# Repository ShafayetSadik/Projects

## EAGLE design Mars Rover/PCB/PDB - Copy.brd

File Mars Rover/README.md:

# Mars Rover

## Overview

Mars rover team designs, builds, and tests a semi-autonomous robotic system for simulated Mars exploration challenges. The rover must drive across rough terrain to GPS waypoints, operate without direct line of sight, manipulate real task panels with a robotic arm, collect and analyze soil or rock samples, deliver or retrieve objects, stream live video to a remote base station, and maintain a reliable wireless communication link for commands, sensor data, and control.

I was responsible for the electrical design and implementation, including PCB design and rover electrical integration. The PCB design files are attached in this repository. I also took part in developing the autonomous system with the software team.

## Autonomous Capability

The autonomy system is a ROS 2-based autonomous navigation stack for a Mars rover. It integrates GPS navigation, Pixhawk heading/GPS data, RealSense camera input, YOLO object detection, ArUco tag tracking, obstacle avoidance, and Arduino motor control into one modular rover system.

The stack is centered around the `local_planner`, which coordinates the rover mission flow. It follows GPS waypoints from the global planner, switches between autonomous and manual modes, starts search behaviors when needed, pauses/resumes perception nodes, and publishes velocity commands to `/cmd_vel`.

## Components Used

- ROS 2 autonomous navigation stack
- GPS waypoint navigation
- Pixhawk GPS, heading, and orientation data
- Arduino motor controller interface
- Intel RealSense camera
- YOLO object detection
- ArUco marker detection and tracking
- Depth-based obstacle avoidance
- Spiral search behavior
- Manual override through ROS 2 topics
- Gazebo and RViz simulation
- Custom ROS 2 messages and services
- Camera stream server
- Electrical design and PCB implementation
- Rover power and control PCB designs
- Robotic arm electrical design
- Wireless command, video, and sensor communication system

## Autonomous System Overview

### Main Features

- GPS waypoint navigation using mission targets from CSV
- Global and local planning for autonomous rover movement
- Pixhawk-based GPS and heading publishing
- Arduino serial interface for rover motor control
- RealSense camera support for depth sensing
- YOLO-based object detection for mission objects
- ArUco tag tracking and approach behavior
- Spiral search pattern for finding objects or tags near target locations
- Optional obstacle avoidance using depth data
- Manual override through ROS 2 topics
- Gazebo/RViz simulation support
- Custom ROS 2 messages and services for rover-specific data

### System Flow

1. Mission targets are loaded from `autonomous_nav/resource/targets.csv`.
2. `global_planner` publishes the target list as `/global_plan`.
3. `local_planner` follows each GPS waypoint using `/gps/fix` and heading data.
4. When a target is reached, the rover starts either object search or ArUco search.
5. `spiral_search` generates a GPS-based search pattern around the target area.
6. YOLO or ArUco tracking pauses the search when a target is detected and guides the rover toward it.
7. Movement commands are published to `/cmd_vel`.
8. `cmd_to_serial` sends rover velocity commands to the Arduino motor controller.

### Major Packages

- `autonomous_nav` - global planner, local planner, target handling, serial motor command bridge
- `pixhawk` - GPS, heading, and orientation publishing from Pixhawk
- `spiral_search` - GPS-based spiral search behavior
- `yolo_detection` - YOLO object detection with RealSense/USB camera input
- `aruco` - ArUco marker detection and approach control
- `obstacle_avoidance` - depth-image-based safe path and avoidance logic
- `custom_interfaces` - custom ROS 2 messages and services
- `cam_stream` - camera stream server
- `odometry` and `path_tracer` - rover path and odometry utilities
- `articubot_one` - Gazebo/RViz simulation package
- `realsense-ros` - Intel RealSense ROS 2 camera driver

## Preview

### Images

### PCB Designs

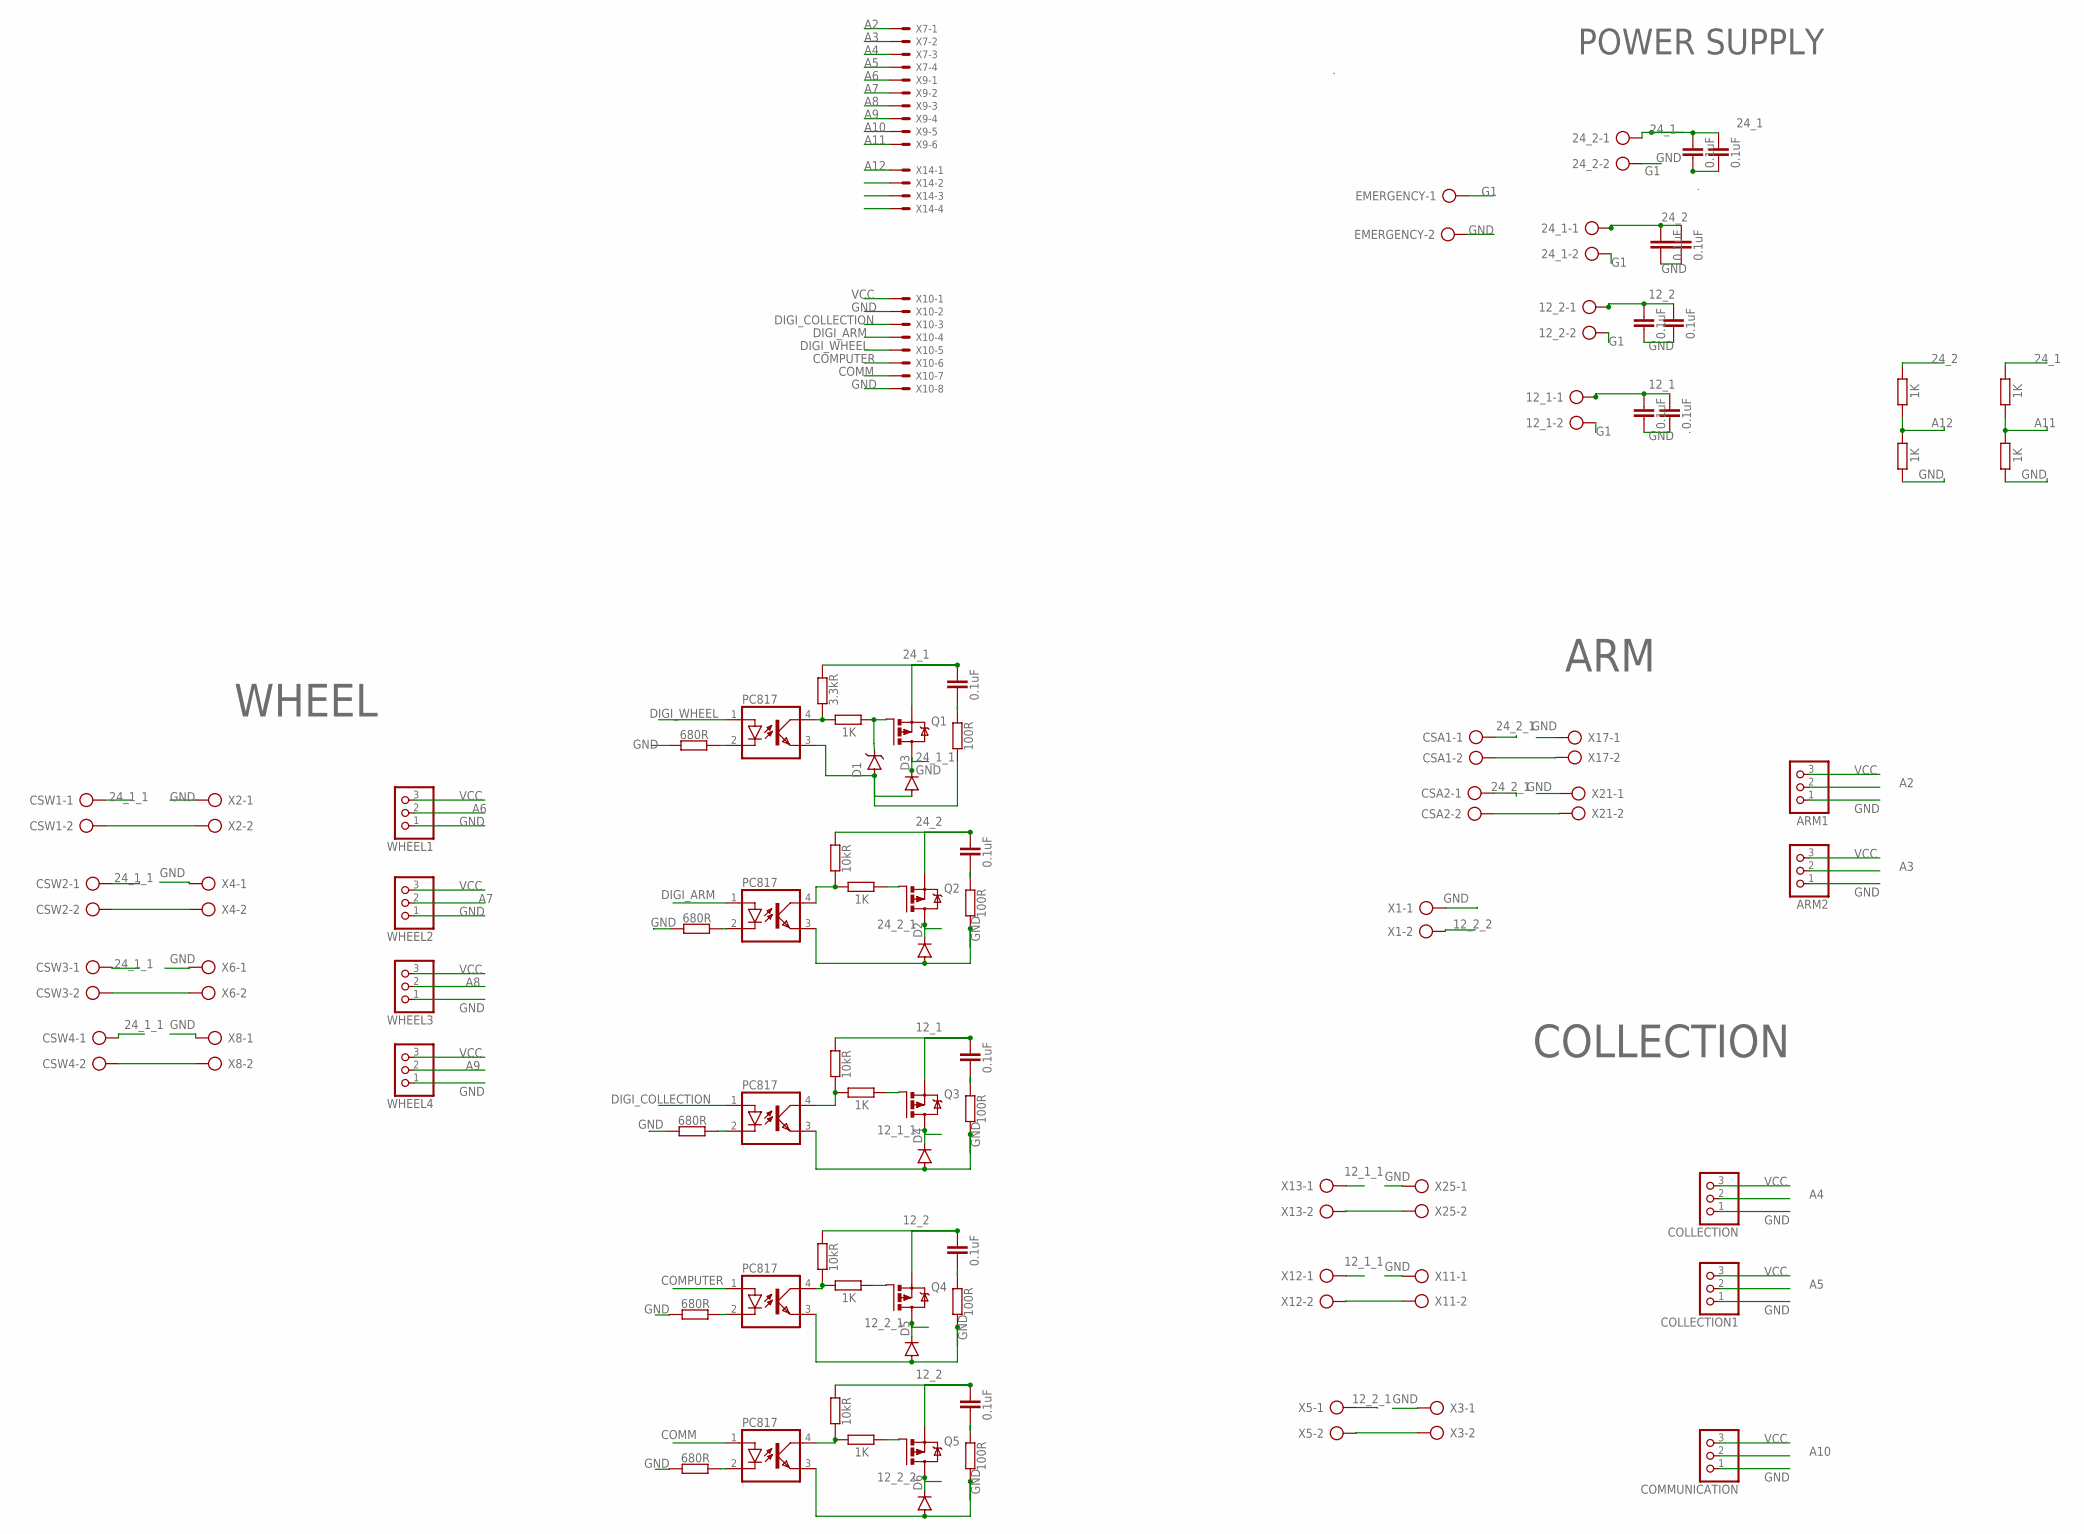
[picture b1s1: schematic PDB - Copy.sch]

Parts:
12_1, 12_2, 24_1, 24_2: AK300/2
ARM1, ARM2: PINHD-1X3; 1X03
C1, C2, C3, C4, C5, C6, C7, C8, C9, C10, C11, C18, C19: 0.1uF; C1206
COLLECTION, COLLECTION1: PINHD-1X3; 1X03
COMMUNICATION: PINHD-1X3; 1X03
CSA1, CSA2: AK300/2
CSW1, CSW2, CSW3, CSW4: AK300/2
D1: 1N4740A-TR; DO-41
D2, D3, D4, D5, D6: 1N4942; DO41-10
EMERGENCY: AK300/2
OK1, OK2, OK3, OK4, OK5: PC817; DIL04
Q1, Q2, Q3, Q4, Q5: PMOSFET-BACKUP_TO220; TO220BV
R1, R5, R9, R13, R24: 680R; R1206
R2, R7, R11, R15, R17, R18, R19, R20, R22: 1K; R1206
R3: 3.3kR; R1206
R4, R6, R10, R14, R21: 100R; R1206
R8, R12, R16, R23: 10kR; R1206
WHEEL1, WHEEL2, WHEEL3, WHEEL4: PINHD-1X3; 1X03
X1, X2, X3, X4, X5, X6, X8, X11, X12, X13, X17, X21, X25: AK300/2
X7, X14: JST-XH-04-PIN-LONG-PAD; JST-XH-04-PACKAGE-LONG-PAD
X9: JST-XH-06-PIN-LONG-PAD; JST-XH-06-PACKAGE-LONG-PAD
X10: JST-XH-08-PIN-LONG-PAD; JST-XH-08-PACKAGE-LONG-PAD

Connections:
12_1: 12_1.1, C3.2, C9.2, C10.2, Q3.S, R12.2
12_1_1: D4.C, Q3.D, X12.1, X13.1
12_2: 12_2.1, C4.2, C5.2, C6.2, C11.2, Q4.S, Q5.S, R16.2, R23.2
12_2_1: D5.C, Q4.D, X5.1
12_2_2: D6.C, Q5.D, X1.2
24_1: 24_2.1, C1.2, C7.2, C8.2, Q1.S, R3.2, R19.2
24_1_1: CSW1.1, CSW2.1, CSW3.1, CSW4.1, D3.C, Q1.D
24_2: 24_1.1, C2.2, C18.2, C19.2, Q2.S, R8.2, R17.2
24_2_1: CSA1.1, CSA2.1, D2.C, Q2.D
A2: ARM1.2, X7.1
A3: ARM2.2, X7.2
A4: COLLECTION.2, X7.3
A5: COLLECTION1.2, X7.4
A6: WHEEL1.2, X9.1
A7: WHEEL2.2, X9.2
A8: WHEEL3.2, X9.3
A9: WHEEL4.2, X9.4
A10: COMMUNICATION.2, X9.5
A11: R19.1, R20.2, X9.6
A12: R17.1, R18.2, X14.1
COMM: OK5.1 (A), X10.7
COMPUTER: OK4.1 (A), X10.6
DIGI_ARM: OK2.1 (A), X10.4
DIGI_COLLECTION: OK3.1 (A), X10.3
DIGI_WHEEL: OK1.1 (A), X10.5
G1: 12_1.2, 12_2.2, 24_1.2, 24_2.2, EMERGENCY.1
GND: ARM1.1, ARM2.1, C5.1, C6.1, C7.1, C8.1, C9.1, C10.1, C18.1, C19.1, COLLECTION.1, COLLECTION1.1, COMMUNICATION.1, D1.A, D2.A, D3.A, D4.A, D5.A, D6.A, EMERGENCY.2, OK1.3 (EMIT), OK2.3 (EMIT), OK3.3 (EMIT), OK4.3 (EMIT), OK5.3 (EMIT), R1.2, R4.1, R5.2, R6.1, R9.2, R10.1, R13.2, R14.1, R18.1, R20.1, R21.1, R24.2, WHEEL1.1, WHEEL2.1, WHEEL3.1, WHEEL4.1, X1.1, X2.1, X3.1, X4.1, X6.1, X8.1, X10.2, X10.8, X11.1, X17.1, X21.1, X25.1
unnamed: OK1.4 (COL), R2.1, R3.1
unnamed: OK4.2 (C), R13.1
unnamed: OK3.2 (C), R9.1
unnamed: OK2.4 (COL), R7.1, R8.1
unnamed: C2.1, R6.2
unnamed: OK3.4 (COL), R11.1, R12.1
unnamed: C4.1, R14.2
unnamed: C3.1, R10.2
unnamed: Q4.G, R15.2
unnamed: OK4.4 (COL), R15.1, R16.1
unnamed: C11.1, R21.2
unnamed: OK5.4 (COL), R22.1, R23.1
unnamed: Q5.G, R22.2
unnamed: OK2.2 (C), R5.1
unnamed: OK1.2 (C), R1.1
unnamed: X11.2, X12.2
unnamed: Q2.G, R7.2
unnamed: OK5.2 (C), R24.1
unnamed: Q3.G, R11.2
unnamed: CSW1.2, X2.2
unnamed: CSW2.2, X4.2
unnamed: C1.1, R4.2
unnamed: D1.C, Q1.G, R2.2
unnamed: CSW3.2, X6.2
unnamed: CSW4.2, X8.2
unnamed: CSA1.2, X17.2
unnamed: CSA2.2, X21.2
unnamed: X13.2, X25.2
unnamed: X3.2, X5.2
VCC: ARM1.3, ARM2.3, COLLECTION.3, COLLECTION1.3, COMMUNICATION.3, WHEEL1.3, WHEEL2.3, WHEEL3.3, WHEEL4.3, X10.1

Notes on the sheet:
WHEEL
ARM
COLLECTION
POWER SUPPLY

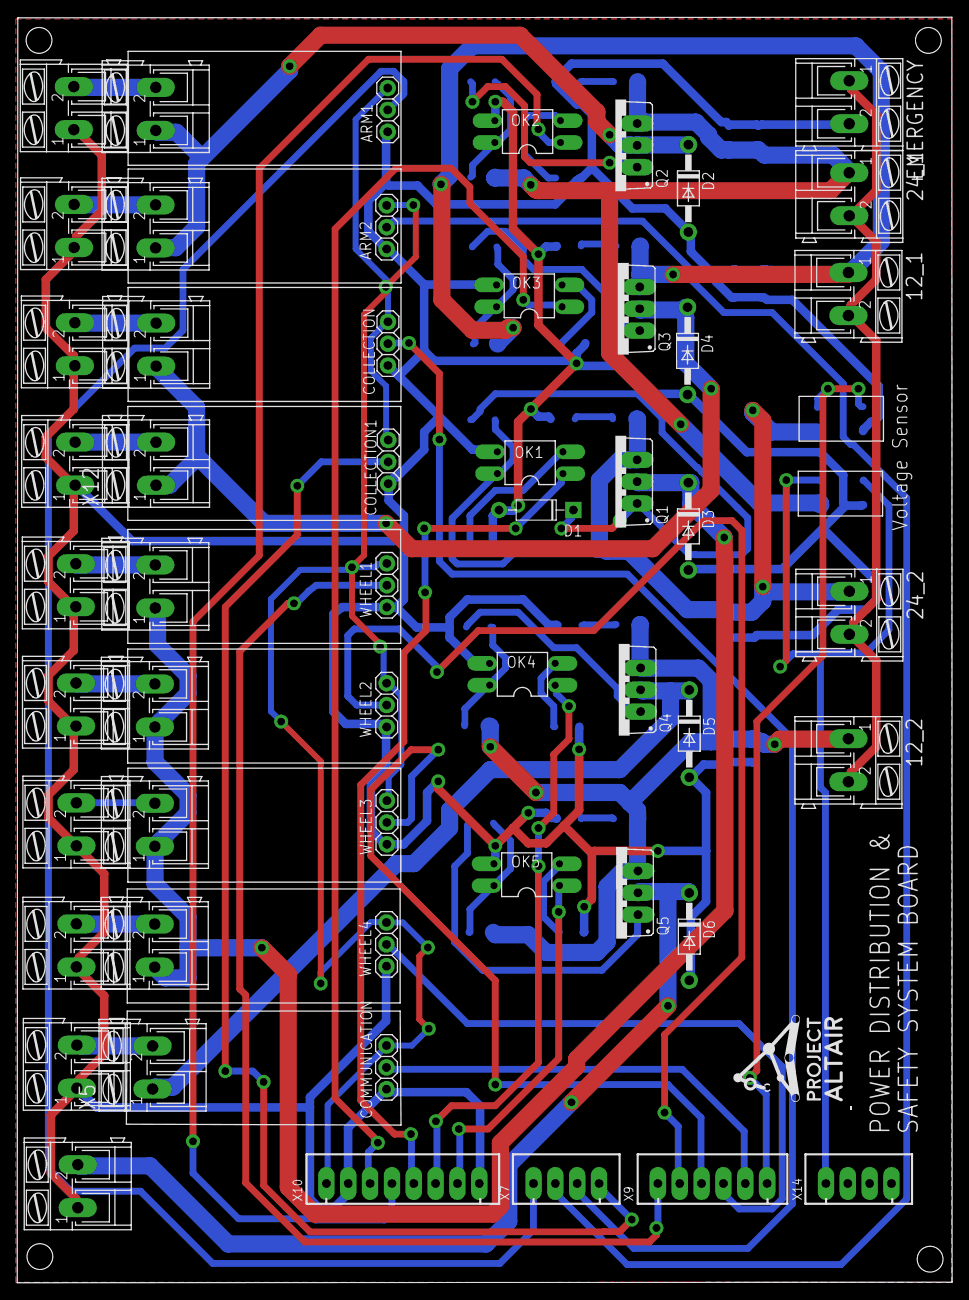
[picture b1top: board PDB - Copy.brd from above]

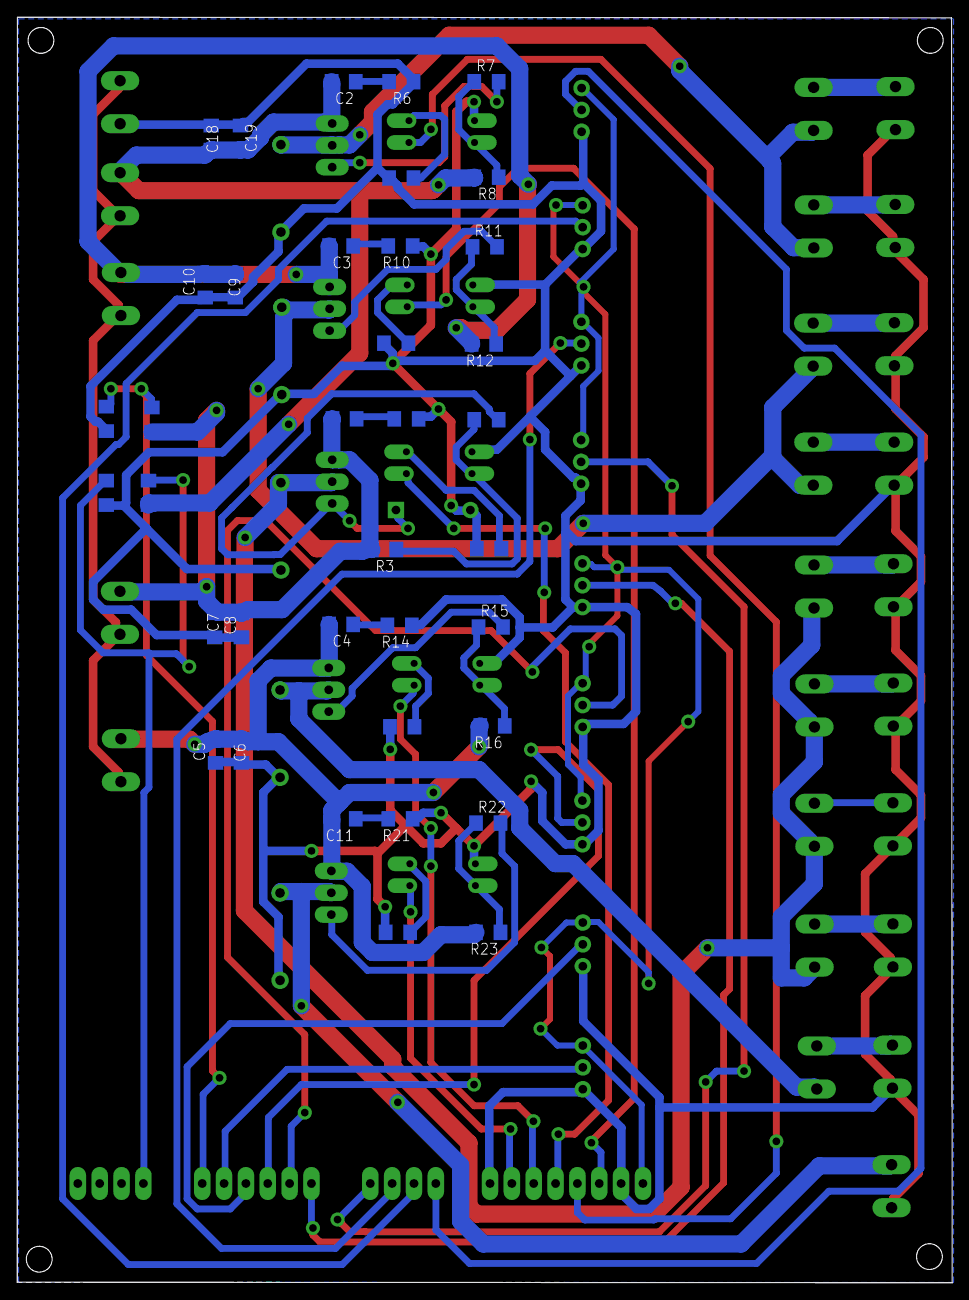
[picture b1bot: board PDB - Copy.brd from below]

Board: 2 copper layers, 108.7 x 147.1 mm, 91 parts (37 on the bottom side), 57 nets.

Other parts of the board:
U$2: ALTAIR

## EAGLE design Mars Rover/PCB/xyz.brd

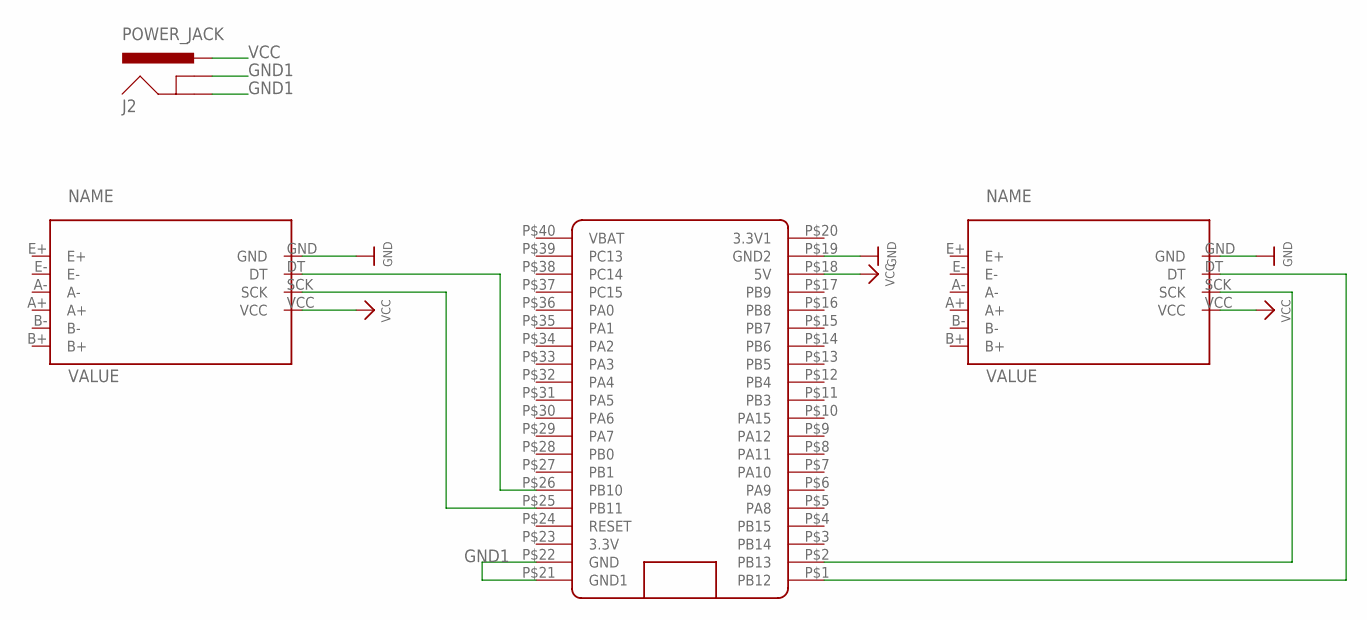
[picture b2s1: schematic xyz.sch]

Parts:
J2: POWER_JACK
U$1, U$2: HX711A; HX711
U$3: BLUE_PILL

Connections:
GND: U$1.GND, U$2.GND, U$3.P$19 (GND2)
GND1: J2.GNDBREAK, U$3.P$21 (GND1), U$3.P$22 (GND)
unnamed: U$1.DT, U$3.P$26 (PB10)
unnamed: U$1.SCK, U$3.P$25 (PB11)
unnamed: U$2.SCK, U$3.P$2 (PB13)
unnamed: U$2.DT, U$3.P$1 (PB12)
VCC: J2.PWR, U$1.VCC, U$2.VCC, U$3.P$18 (5V)

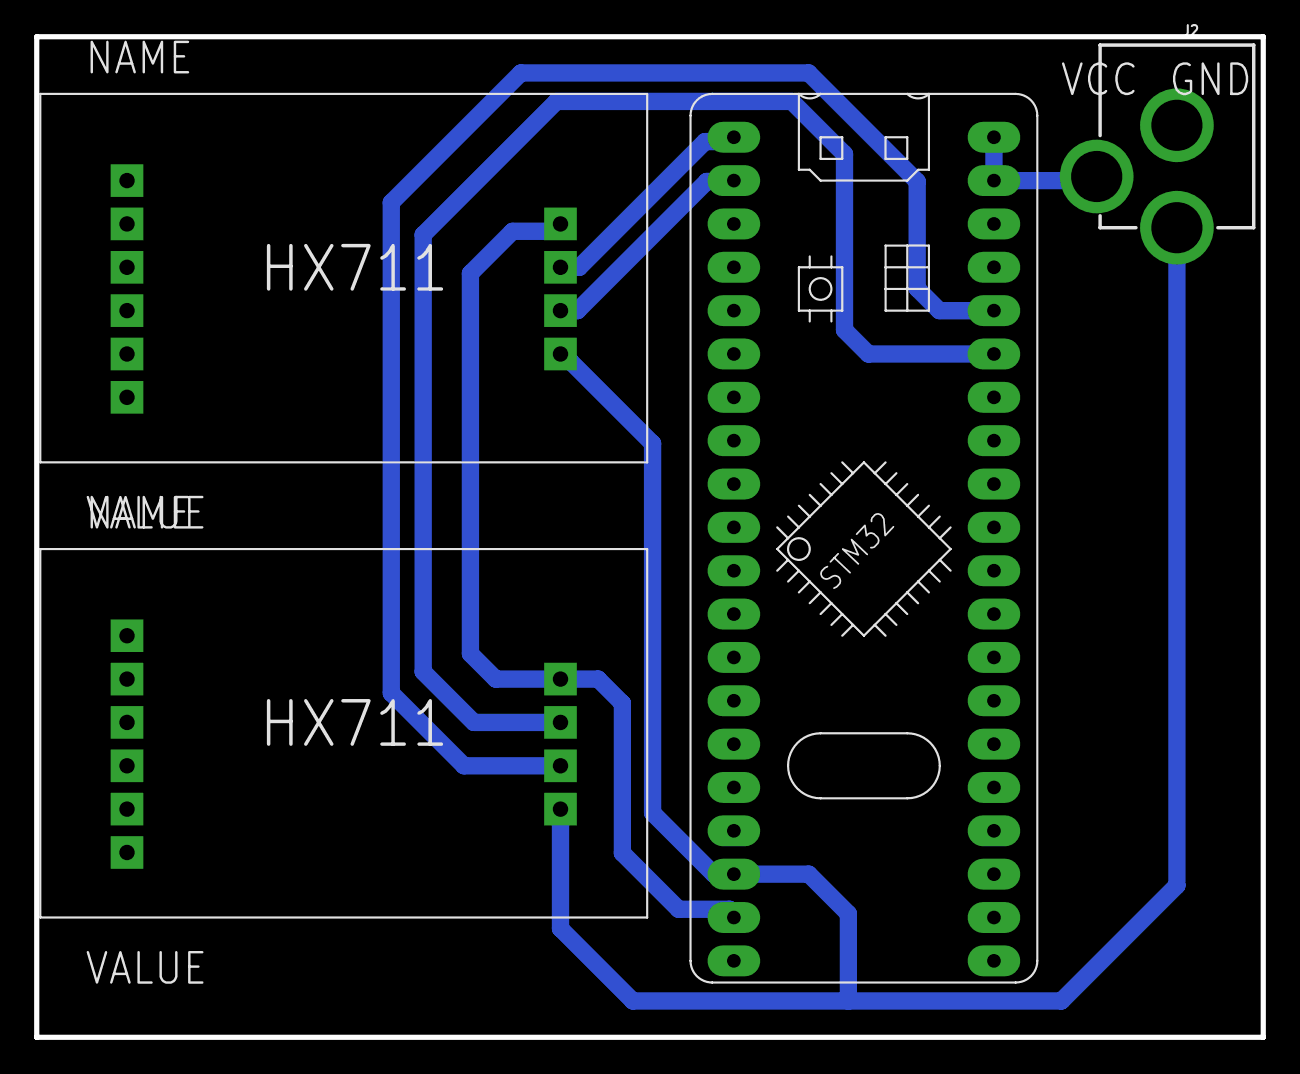
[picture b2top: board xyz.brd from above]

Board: 2 copper layers, 71.9 x 58.6 mm, 4 parts (0 on the bottom side), 7 nets.

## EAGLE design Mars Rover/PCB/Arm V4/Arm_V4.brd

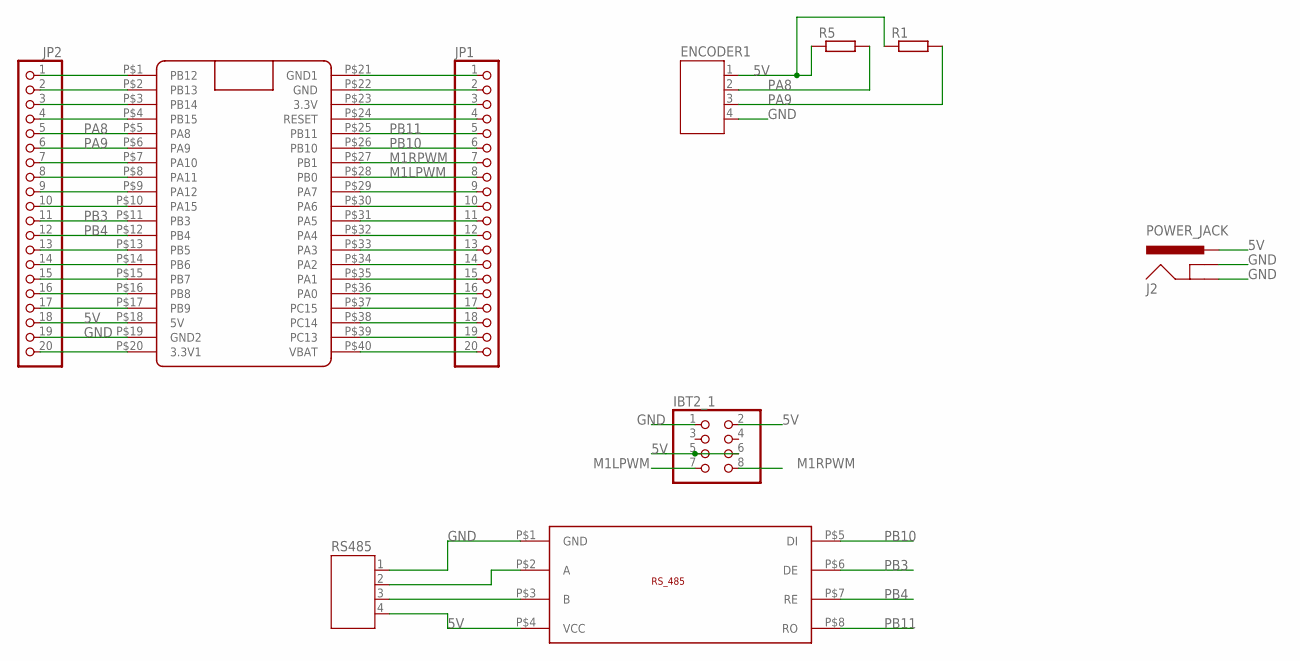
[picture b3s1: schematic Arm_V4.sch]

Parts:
ENCODER1: JST-PH4
IBT2_1: PINHD-2X4; 2X04
J2: POWER_JACK
JP1, JP2: PINHD-1X20; 1X20
R1, R5: R-EU_0207/10; 0207/10
RS485: JST-PH4
U$1: BLUE_PILL
U$2: RS_485PCB; RSS485PCB

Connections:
5V: ENCODER1.1, IBT2_1.2, IBT2_1.5, IBT2_1.6, J2.PWR, JP2.18, R1.1, R5.1, RS485.4, U$1.P$18 (5V), U$2.P$4 (VCC)
GND: ENCODER1.4, IBT2_1.1, J2.GNDBREAK, JP2.19, RS485.1, U$1.P$19 (GND2), U$2.P$1 (GND)
M1LPWM: IBT2_1.7, JP1.8, U$1.P$28 (PB0)
M1RPWM: IBT2_1.8, JP1.7, U$1.P$27 (PB1)
unnamed: JP1.1, U$1.P$21 (GND1)
unnamed: JP1.2, U$1.P$22 (GND)
unnamed: JP1.3, U$1.P$23 (3.3V)
unnamed: JP1.4, U$1.P$24 (RESET)
unnamed: JP1.9, U$1.P$29 (PA7)
unnamed: JP1.10, U$1.P$30 (PA6)
unnamed: JP2.14, U$1.P$14 (PB6)
unnamed: JP2.15, U$1.P$15 (PB7)
unnamed: RS485.2, U$2.P$2 (A)
unnamed: JP1.11, U$1.P$31 (PA5)
unnamed: JP1.12, U$1.P$32 (PA4)
unnamed: JP1.13, U$1.P$33 (PA3)
unnamed: JP1.14, U$1.P$34 (PA2)
unnamed: JP1.15, U$1.P$35 (PA1)
unnamed: JP1.16, U$1.P$36 (PA0)
unnamed: JP1.17, U$1.P$37 (PC15)
unnamed: JP1.18, U$1.P$38 (PC14)
unnamed: JP1.19, U$1.P$39 (PC13)
unnamed: JP1.20, U$1.P$40 (VBAT)
unnamed: JP2.1, U$1.P$1 (PB12)
unnamed: JP2.2, U$1.P$2 (PB13)
unnamed: JP2.3, U$1.P$3 (PB14)
unnamed: JP2.4, U$1.P$4 (PB15)
unnamed: RS485.3, U$2.P$3 (B)
unnamed: JP2.7, U$1.P$7 (PA10)
unnamed: JP2.8, U$1.P$8 (PA11)
unnamed: JP2.9, U$1.P$9 (PA12)
unnamed: JP2.10, U$1.P$10 (PA15)
unnamed: JP2.13, U$1.P$13 (PB5)
unnamed: JP2.16, U$1.P$16 (PB8)
unnamed: JP2.17, U$1.P$17 (PB9)
unnamed: JP2.20, U$1.P$20 (3.3V1)
PA8: ENCODER1.2, JP2.5, R5.2, U$1.P$5 (PA8)
PA9: ENCODER1.3, JP2.6, R1.2, U$1.P$6 (PA9)
PB3: JP2.11, U$1.P$11 (PB3), U$2.P$6 (DE)
PB4: JP2.12, U$1.P$12 (PB4), U$2.P$7 (RE)
PB10: JP1.6, U$1.P$26 (PB10), U$2.P$5 (DI)
PB11: JP1.5, U$1.P$25 (PB11), U$2.P$8 (RO)

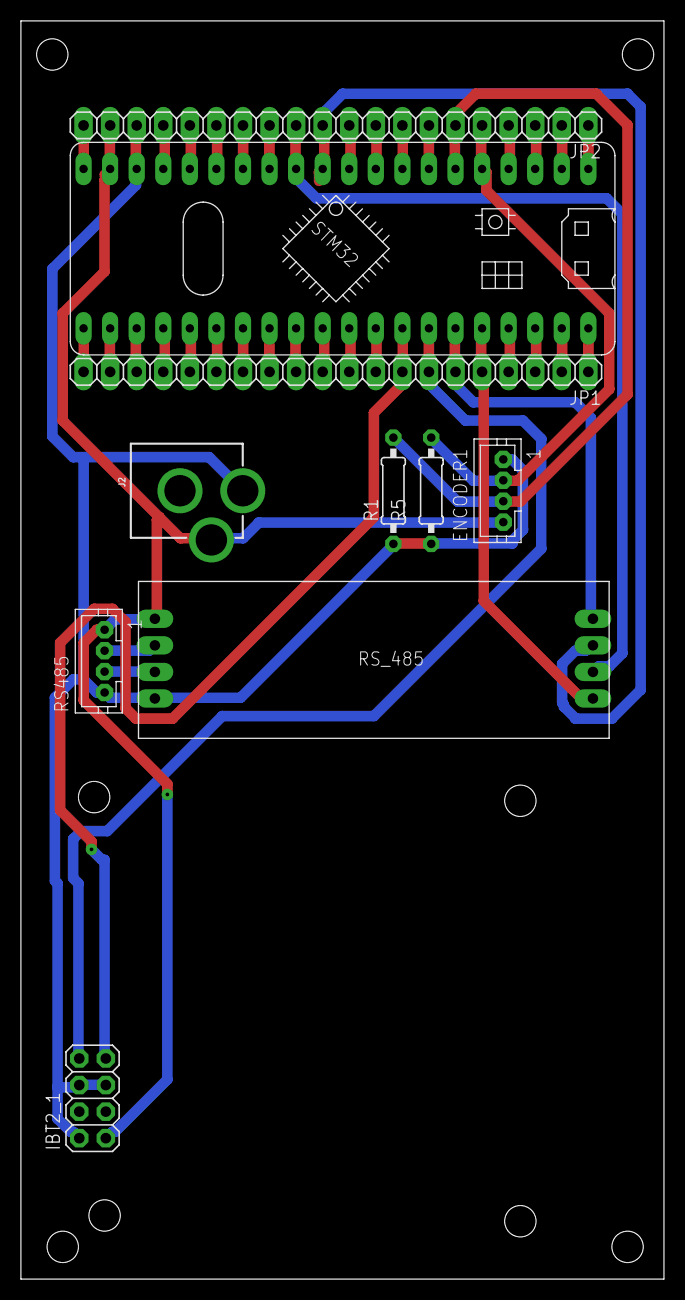
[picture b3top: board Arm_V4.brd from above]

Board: 2 copper layers, 61.5 x 120.3 mm, 10 parts (0 on the bottom side), 42 nets.

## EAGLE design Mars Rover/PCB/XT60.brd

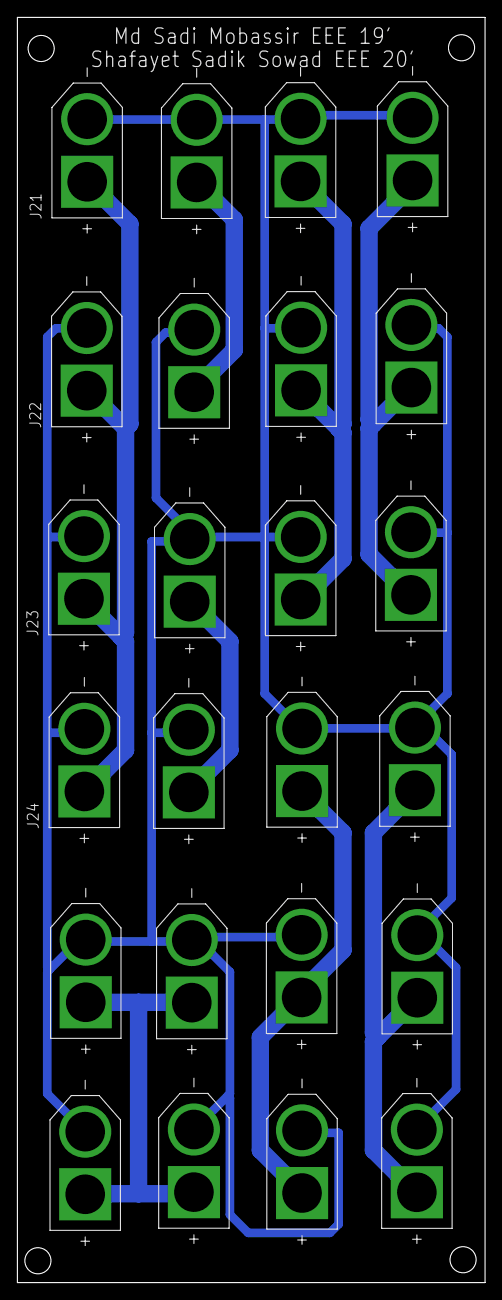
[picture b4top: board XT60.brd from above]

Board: 2 copper layers, 53.8 x 145.5 mm, 24 parts (0 on the bottom side), 9 nets.

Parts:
J1, J2, J3, J4, J5, J6, J7, J8, J9, J10, J11, J12, J13, J14, J15, J16, J17, J18, J19, J20, J21, J22, J23, J24: XT60-M; AMASS_XT60-M

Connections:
A: J1.P, J2.P, J3.P
B: J4.P, J5.P, J6.P
C: J7.P, J8.P, J9.P
D: J10.P, J11.P, J12.P
E: J13.P, J14.P
F: J15.P, J16.P
G: J17.P, J18.P, J19.P, J20.P
GND: J1.N, J2.N, J3.N, J4.N, J5.N, J6.N, J7.N, J8.N, J9.N, J10.N, J11.N, J12.N, J13.N, J14.N, J15.N, J16.N, J17.N, J18.N, J19.N, J20.N, J21.N, J22.N, J23.N, J24.N
H: J21.P, J22.P, J23.P, J24.P

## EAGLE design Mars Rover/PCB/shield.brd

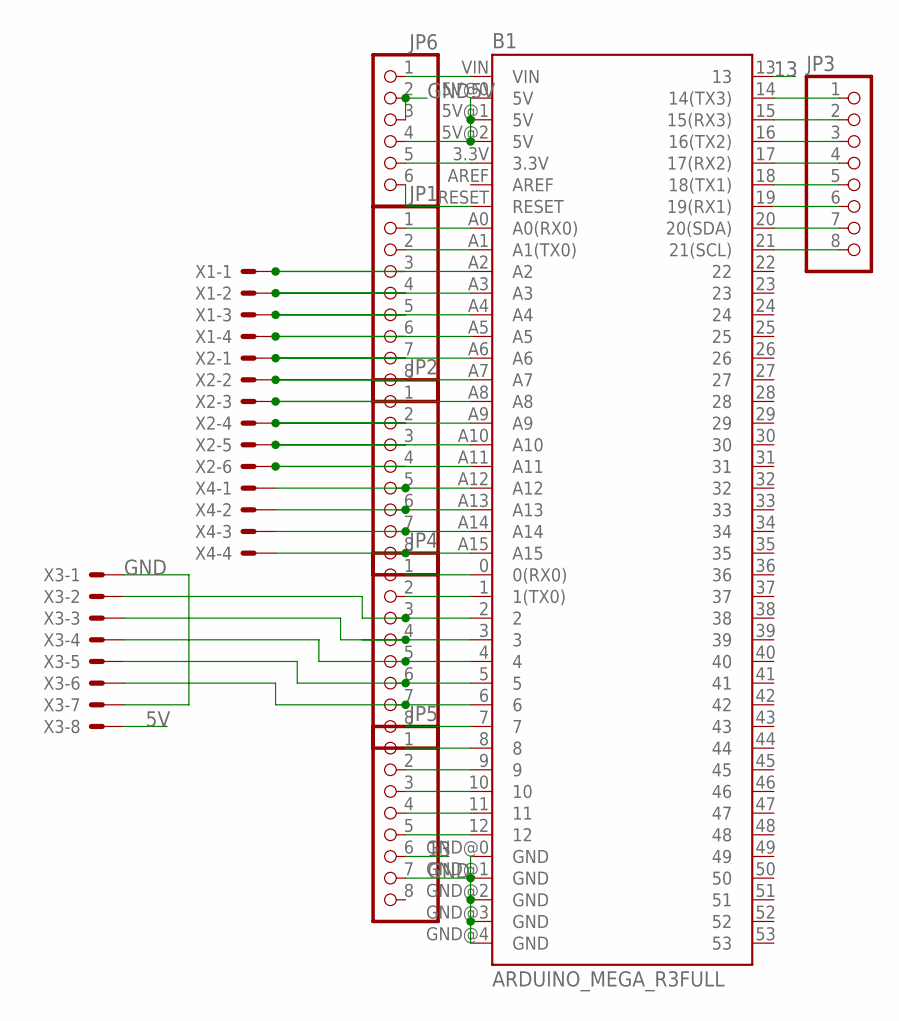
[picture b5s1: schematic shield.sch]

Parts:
B1: ARDUINO_MEGA_R3FULL; ARDUINO_MEGA
JP1, JP2, JP3, JP4, JP5: PINHD-1X8; 1X08
JP6: PINHD-1X6; 1X06
X1, X4: JST-XH-04-PIN-LONG-PAD; JST-XH-04-PACKAGE-LONG-PAD
X2: JST-XH-06-PIN-LONG-PAD; JST-XH-06-PACKAGE-LONG-PAD
X3: JST-XH-08-PIN-LONG-PAD; JST-XH-08-PACKAGE-LONG-PAD

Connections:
5V: B1.5V@0 (5V), B1.5V@1 (5V), B1.5V@2 (5V), JP6.4, X3.8
13: B1.13, JP5.6
GND: B1.GND@0 (GND), B1.GND@1 (GND), B1.GND@2 (GND), B1.GND@3 (GND), B1.GND@4 (GND), JP5.7, JP6.2, JP6.3, X3.1, X3.7
unnamed: B1.A0 (A0(RX0)), JP1.1
unnamed: B1.A1 (A1(TX0)), JP1.2
unnamed: B1.A2, JP1.3, X1.1
unnamed: B1.A3, JP1.4, X1.2
unnamed: B1.A4, JP1.5, X1.3
unnamed: B1.A5, JP1.6, X1.4
unnamed: B1.A6, JP1.7, X2.1
unnamed: B1.A7, JP1.8, X2.2
unnamed: B1.A8, JP2.1, X2.3
unnamed: B1.A9, JP2.2, X2.4
unnamed: B1.A10, JP2.3, X2.5
unnamed: B1.A11, JP2.4, X2.6
unnamed: B1.A12, JP2.5, X4.1
unnamed: B1.A13, JP2.6, X4.2
unnamed: B1.A14, JP2.7, X4.3
unnamed: B1.A15, JP2.8, X4.4
unnamed: B1.14 (14(TX3)), JP3.1
unnamed: B1.15 (15(RX3)), JP3.2
unnamed: B1.16 (16(TX2)), JP3.3
unnamed: B1.17 (17(RX2)), JP3.4
unnamed: B1.18 (18(TX1)), JP3.5
unnamed: B1.19 (19(RX1)), JP3.6
unnamed: B1.20 (20(SDA)), JP3.7
unnamed: B1.21 (21(SCL)), JP3.8
unnamed: B1.0 (0(RX0)), JP4.1
unnamed: B1.1 (1(TX0)), JP4.2
unnamed: B1.2, JP4.3, X3.2
unnamed: B1.4, JP4.5, X3.4
unnamed: B1.7, JP4.8
unnamed: B1.8, JP5.1
unnamed: B1.9, JP5.2
unnamed: B1.10, JP5.3
unnamed: B1.11, JP5.4
unnamed: B1.12, JP5.5
unnamed: B1.VIN, JP6.1
unnamed: B1.3.3V, JP6.5
unnamed: B1.RESET, JP6.6
unnamed: B1.3, JP4.4, X3.3
unnamed: B1.5, JP4.6, X3.5
unnamed: B1.6, JP4.7, X3.6

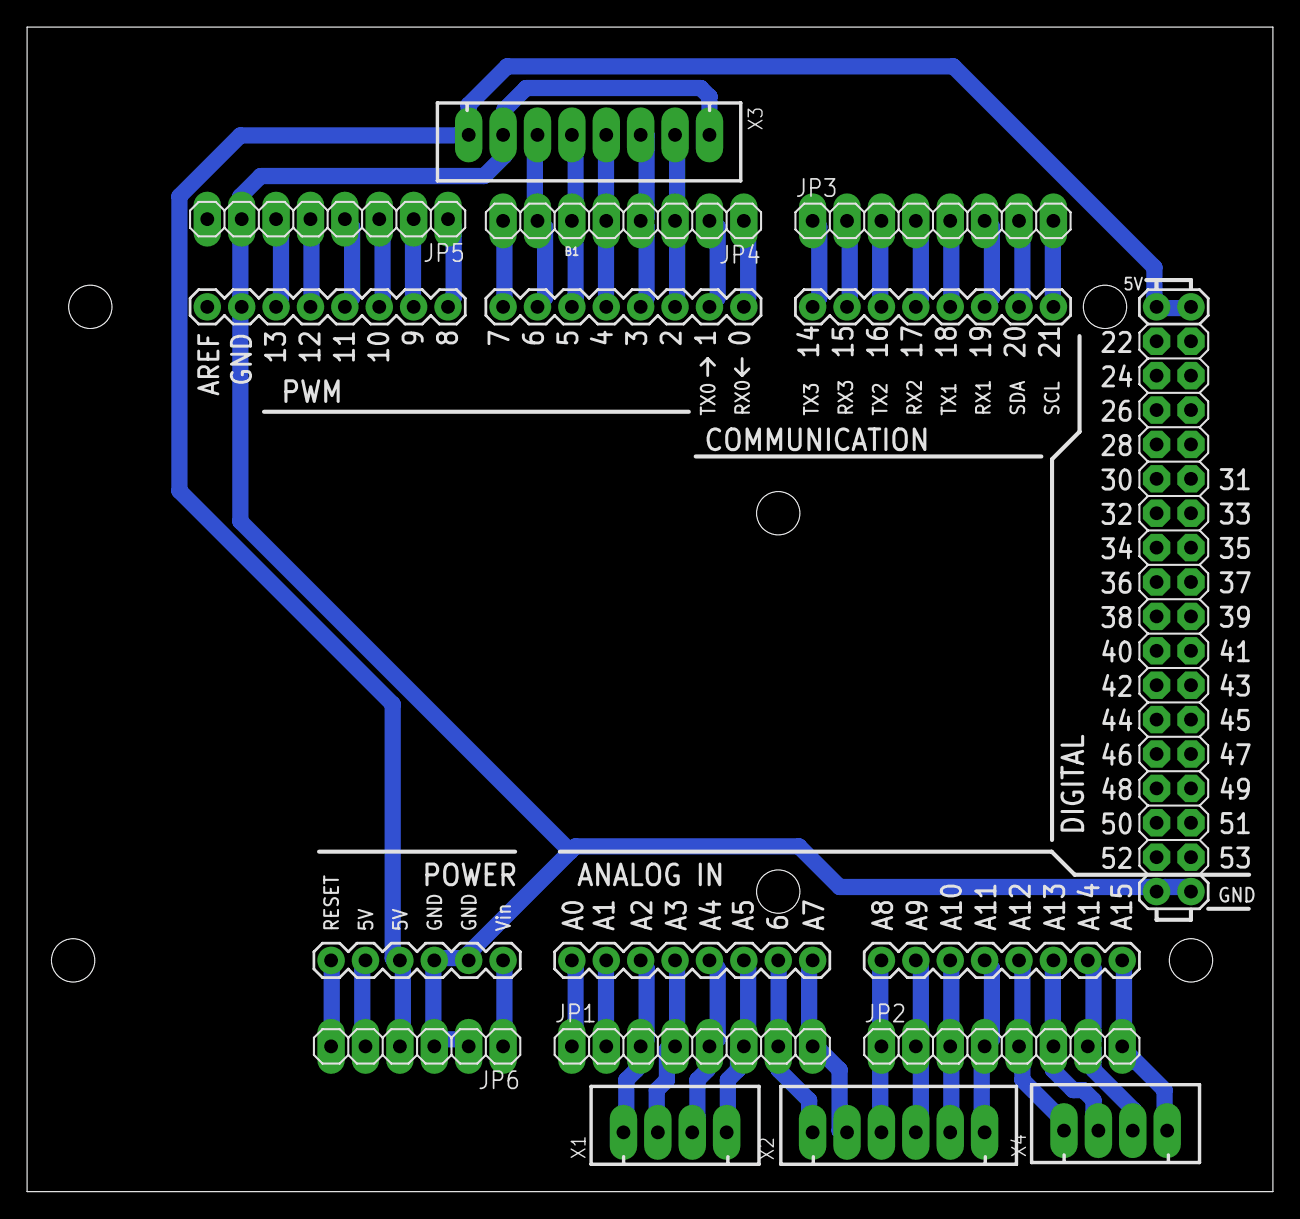
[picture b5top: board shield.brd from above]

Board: 2 copper layers, 92.0 x 86.0 mm, 11 parts (0 on the bottom side), 43 nets.

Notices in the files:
parts and their libraries:
SparkFun-Boards: Licensing: Creative Commons ShareAlike 4.0 International - https://creativecommons.org/licenses/by-sa/4.0
